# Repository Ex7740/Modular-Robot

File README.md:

# Modular Robot

This is going be to be a modular robot 

# Main features

- The ability to have different attachements added and removed
- Uses JST connectors so you can add any attachments and have them be recognised using i2c

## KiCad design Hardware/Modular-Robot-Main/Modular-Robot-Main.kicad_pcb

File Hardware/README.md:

# Hardware 

- Main module 
- Leg module
- Sensor Module (future)

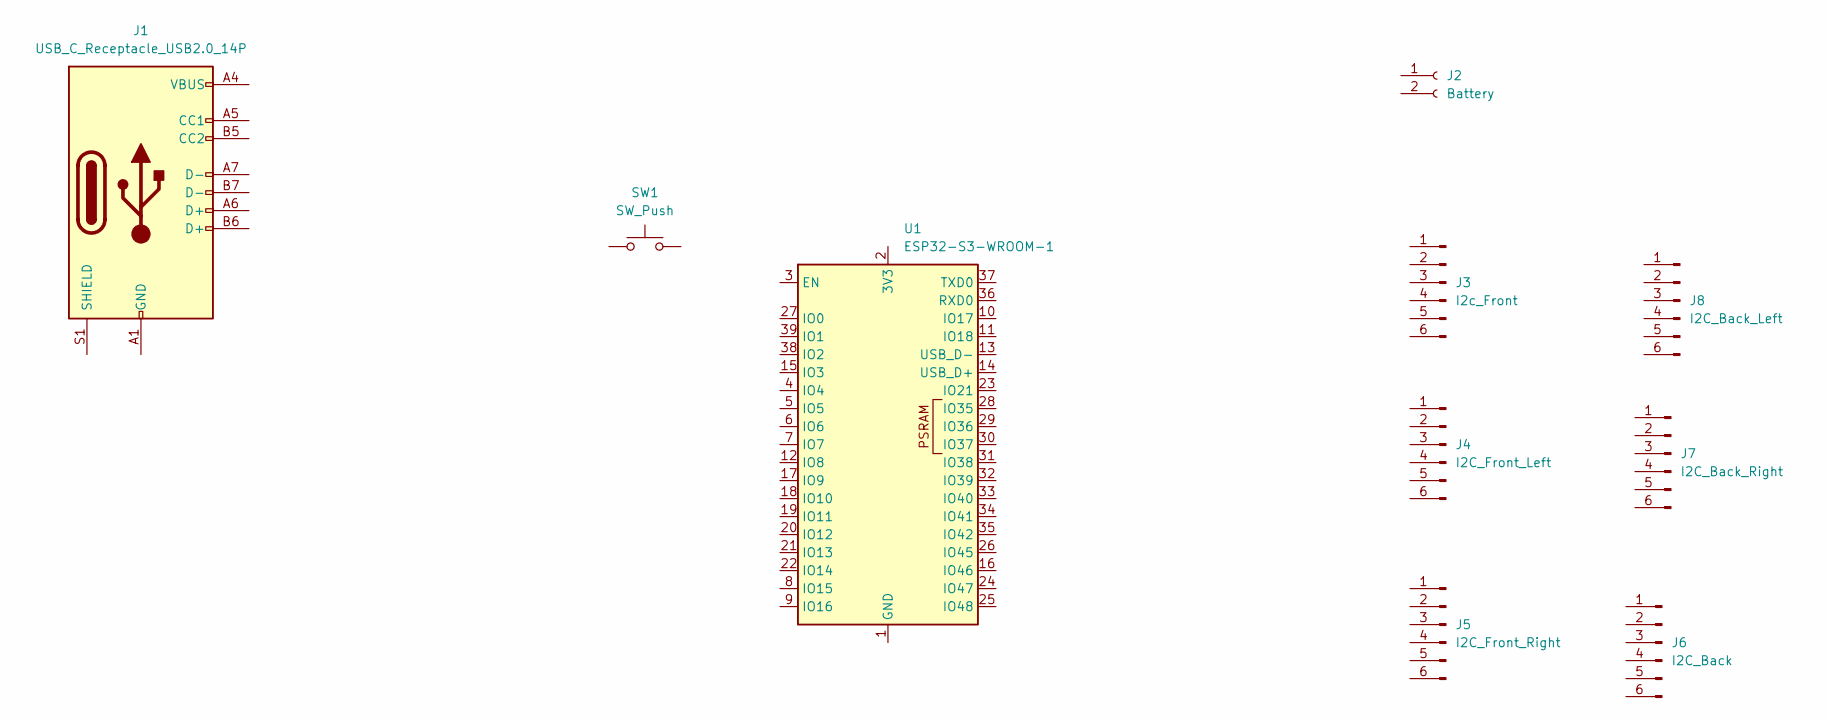
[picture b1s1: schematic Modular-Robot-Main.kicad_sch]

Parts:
J1: USB_C_Receptacle_USB2.0_14P; USB_C_Receptacle_GCT_USB4110
J2: Battery; JST_PH_B2B-PH-K_1x02_P2.00mm_Vertical
J3: I2c_Front; PinHeader_1x06_P2.54mm_Horizontal
J4: I2C_Front_Left; PinHeader_1x06_P2.54mm_Horizontal
J5: I2C_Front_Right; PinHeader_1x06_P2.54mm_Horizontal
J6: I2C_Back; PinHeader_1x06_P2.54mm_Horizontal
J7: I2C_Back_Right; PinHeader_1x06_P2.54mm_Horizontal
J8: I2C_Back_Left; PinHeader_1x06_P2.54mm_Horizontal
SW1: SW_Push; SW_Push_1P1T_NO_CK_KSC6xxJ
U1: ESP32-S3-WROOM-1

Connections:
unnamed: J1.A1 (GND), J1.A12 (GND), J1.B1 (GND), J1.B12 (GND)
unnamed: J1.A4 (VBUS), J1.A9 (VBUS), J1.B4 (VBUS), J1.B9 (VBUS)
unnamed: U1.1 (GND), U1.40 (GND), U1.41 (GND)

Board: 2 copper layers, 10 parts (0 on the bottom side), 3 nets, no tracks yet.

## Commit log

2026-01-16 Added main.py
2026-01-16 Made a code file
2026-01-16 Removed the code as i dont have any ideas for projects right now``
2026-01-16 Testing
2026-01-20 Updated readme and added filestructure
2026-01-20 Updated readme's for different sections
2026-01-20 Added design folder
2026-01-20 Added simulation
2026-01-20 Started on simulation script
2026-01-21 Rough sim finished
2026-01-21 Added left and right attachment points to main body
2026-01-21 changed colour of main body
2026-01-21 Added x offset for new addon
2026-01-22 Created the main module project in kicad
2026-01-22 Updated pcb and schematic
